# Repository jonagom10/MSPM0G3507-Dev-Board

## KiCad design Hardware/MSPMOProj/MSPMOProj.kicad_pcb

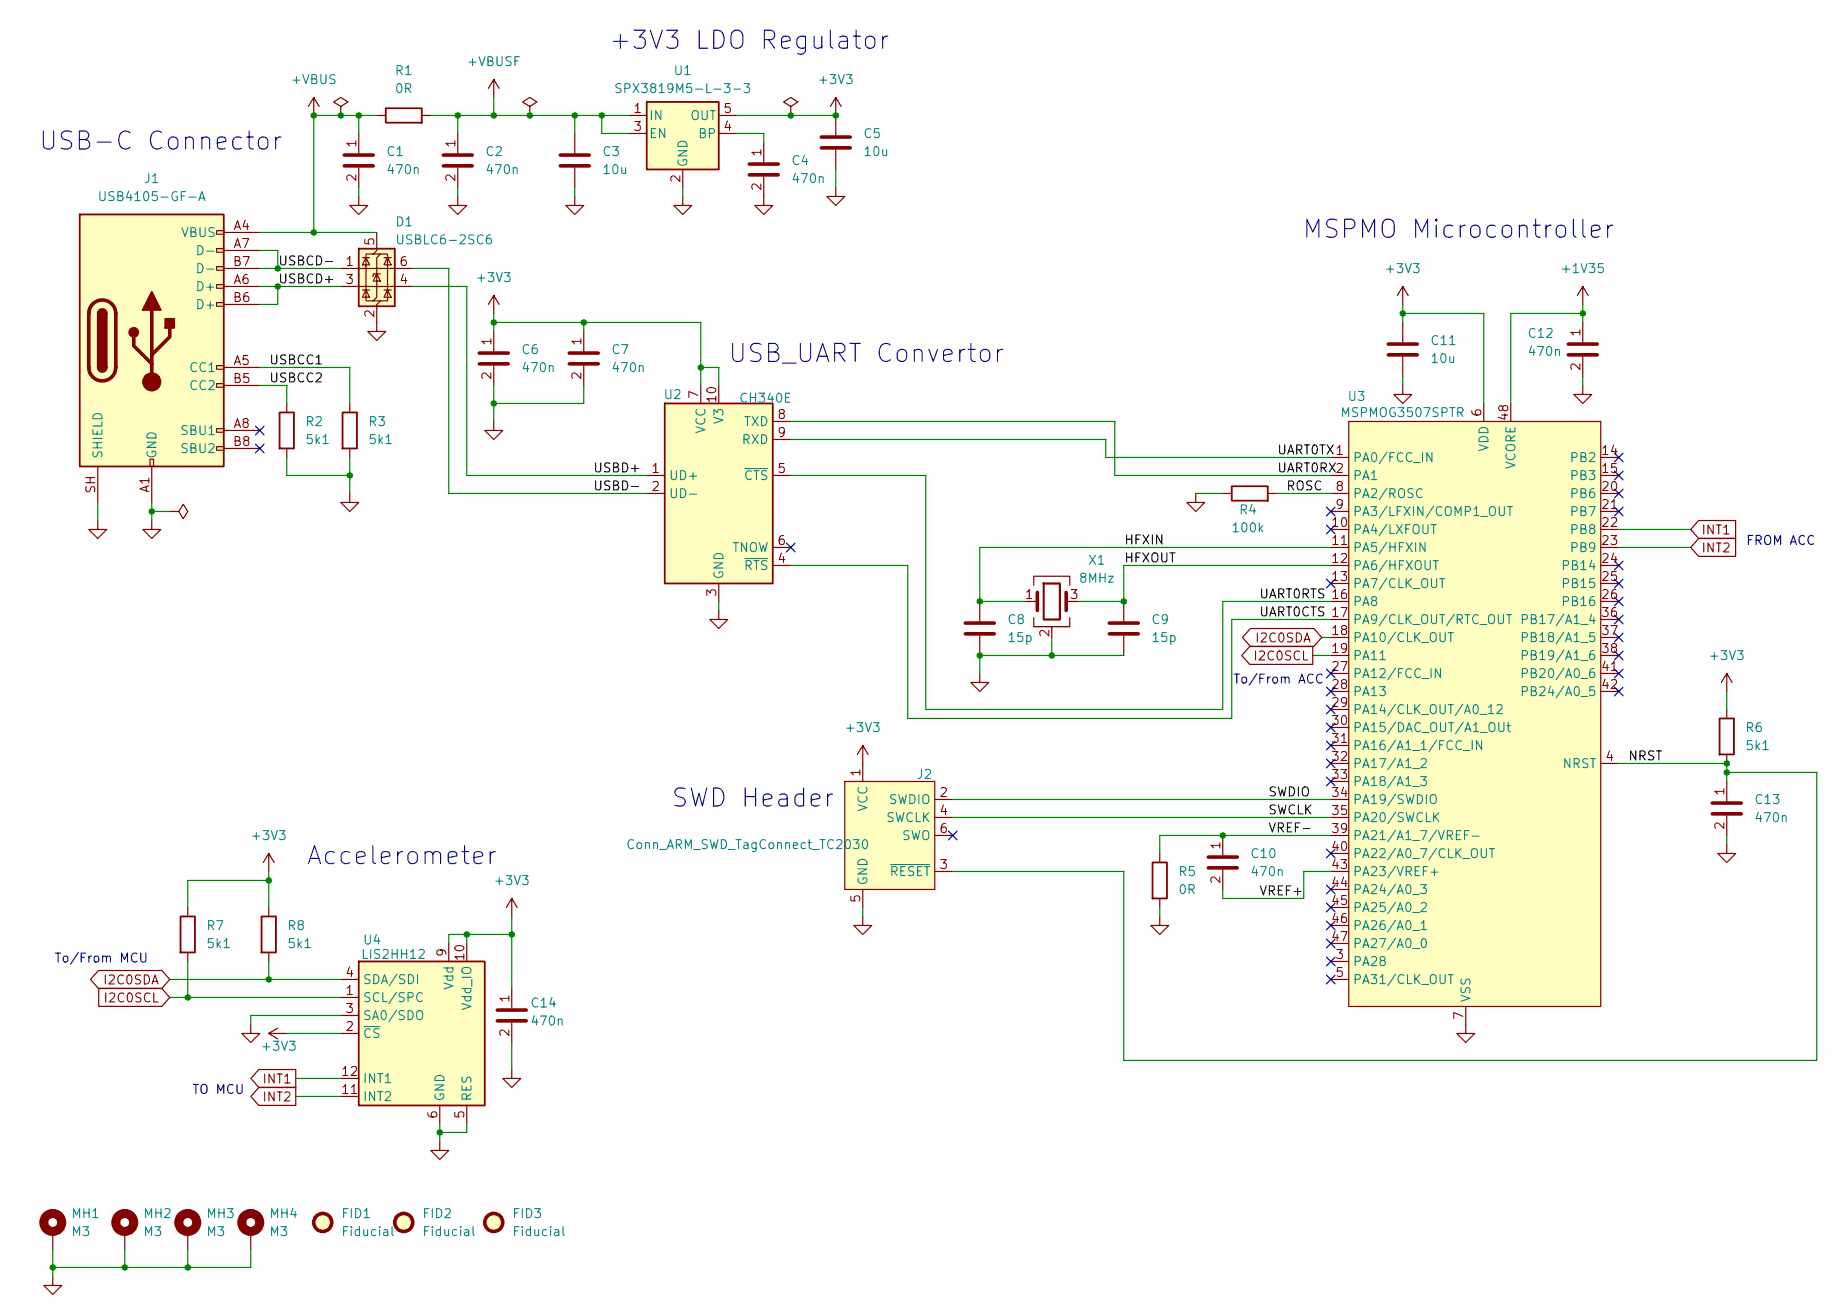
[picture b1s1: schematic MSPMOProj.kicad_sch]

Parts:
C1, C2, C4, C6, C7, C10, C12, C13, C14: 470n; C_0603_1608Metric; Manufacturer Part Number CL10B474KA8NNNC; LCSC Number C1623
C3, C5, C11: 10u; C_0805_2012Metric; Manufacturer Part Number CL21A106KAYNNNE; LCSC C15850
C8, C9: 15p; C_0603_1608Metric; Manufacturer Part Number CL10C150JB8NNNC; LCSC C1644
D1: USBLC6-2SC6; SOT-23-6; Manufacturer Part Number USBLC6-2SC6; LCSC C7519
FID1, FID2, FID3: Fiducial; Fiducial_1mm_Mask2mm
J1: USB4105-GF-A; USB_C_Receptacle_GCT_USB4105-xx-A_16P_TopMnt_Horizontal; Manufacturer Part Number USB4105-GF-A-060; LCSC C3025063
J2: Conn_ARM_SWD_TagConnect_TC2030; Tag-Connect_TC2030-IDC-FP_2x03_P1.27mm_Vertical
MH1, MH2, MH3, MH4: M3; MountingHole_3.2mm_M3_Pad_Via
R1, R5: 0R; R_0603_1608Metric; Manufacturer Part Number 0603WAF0000T5E; LCSC C21189
R2, R3, R6, R7, R8: 5k1; R_0603_1608Metric; Manufacturer Part Number 0603WAF5101T5E; LCSC C23186
R4: 100k; R_0603_1608Metric; Manufacturer Part Number RT0603BRD07100KL; LCSC C122538
U1: SPX3819M5-L-3-3; SOT-23-5; Manufacturer Part Number SPX3819M5-L-3-3/TR; LCSC C9055
U2: CH340E; MSOP-10_3x3mm_P0.5mm; Manufacturer Part Number CH340E; LCSC C99652
U3: MSPMOG3507SPTR; LQFP-48_7x7mm_P0.5mm; Manufacturer Part Number MSPM0G3507SPTR; LCSC C22362630
U4: LIS2HH12; LGA-12_2x2mm_P0.5mm; Manufacturer Part Number LIS2HH12TR; LCSC C221446
X1: 8MHz; Crystal_SMD_3225-4Pin_3.2x2.5mm; Manufacturer Part Number X3S008000FA1H-X; LCSC C254257

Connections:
+1V35: C12.1, U3.48 (VCORE)
+3V3: C5.1, C6.1, C7.1, C11.1, C14.1, J2.1 (VCC), R6.1, R7.1, R8.1, U1.5 (OUT), U2.7 (VCC), U2.10 (V3), U3.6 (VDD), U4.2 (~CS), U4.9 (Vdd), U4.10 (Vdd_IO)
+VBUS: C1.1, D1.5 (VBUS), J1.A4 (VBUS), J1.A9 (VBUS), J1.B4 (VBUS), J1.B9 (VBUS), R1.1
+VBUSF: C2.1, C3.1, R1.2, U1.1 (IN), U1.3 (EN)
/HFXIN: C8.1, U3.11 (PA5/HFXIN), X1.1
/HFXOUT: C9.1, U3.12 (PA6/HFXOUT), X1.3
/NRST: C13.1, J2.3 (~RESET), R6.2, U3.4 (NRST)
/ROSC: R4.2, U3.8 (PA2/ROSC)
/SWCLK: J2.4 (SWCLK), U3.35 (PA20/SWCLK)
/SWDIO: J2.2 (SWDIO), U3.34 (PA19/SWDIO)
/UART0CTS: U2.4 (~RTS), U3.17 (PA9/CLK_OUT/RTC_OUT)
/UART0RTS: U2.5 (~CTS), U3.16 (PA8)
/UART0RX: U2.8 (TXD), U3.2 (PA1)
/UART0TX: U2.9 (RXD), U3.1 (PA0/FCC_IN)
/USBCC1: J1.A5 (CC1), R3.1
/USBCC2: J1.B5 (CC2), R2.1
/USBCD+: D1.3 (I/O2), J1.A6 (D+), J1.B6 (D+)
/USBCD-: D1.1 (I/O1), J1.A7 (D-), J1.B7 (D-)
/USBD+: D1.4 (I/O2), U2.1 (UD+)
/USBD-: D1.6 (I/O1), U2.2 (UD-)
/VREF+: C10.2, U3.43 (PA23/VREF+)
/VREF-: C10.1, R5.1, U3.39 (PA21/A1_7/VREF-)
GND: C1.2, C2.2, C3.2, C4.2, C5.2, C6.2, C7.2, C8.2, C9.2, C11.2, C12.2, C13.2, C14.2, D1.2 (GND), J1.A1 (GND), J1.A12 (GND), J1.B1 (GND), J1.B12 (GND), J1.SH (SHIELD), J2.5 (GND), MH1.1 (1_1), MH2.1 (1_1), MH3.1 (1_1), MH4.1 (1_1), R2.2, R3.2, R4.1, R5.2, U1.2 (GND), U2.3 (GND), U3.7 (VSS), U4.3 (SA0/SDO), U4.5 (RES), U4.6 (GND), U4.7 (GND), U4.8 (GND), X1.2 (G), X1.4 (G)
I2C0SCL: R7.2, U3.19 (PA11), U4.1 (SCL/SPC)
I2C0SDA: R8.2, U3.18 (PA10/CLK_OUT), U4.4 (SDA/SDI)
INT1: U3.22 (PB8), U4.12 (INT1)
INT2: U3.23 (PB9), U4.11 (INT2)
unnamed: C4.1, U1.4 (BP)

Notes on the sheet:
MSPMO Microcontroller
To/From ACC
SWD Header
+3V3 LDO Regulator
USB_UART Convertor
FROM ACC
To/From MCU
USB-C Connector
Accelerometer
TO MCU

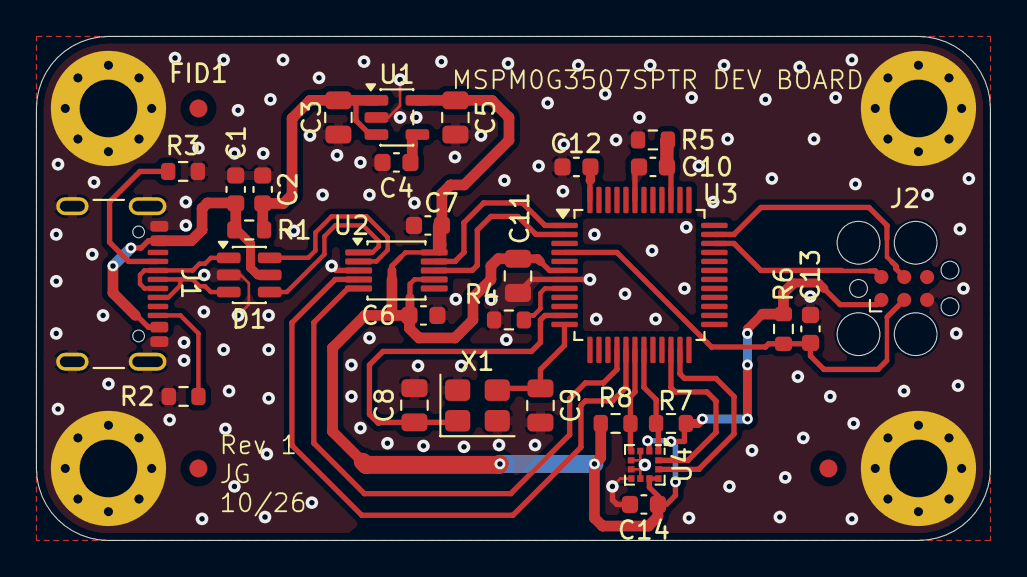
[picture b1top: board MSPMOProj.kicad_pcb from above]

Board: 2 copper layers, 53.0 x 28.0 mm, 37 parts (0 on the bottom side), 28 nets.

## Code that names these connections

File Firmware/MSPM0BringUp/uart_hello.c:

/*
 * Copyright (c) 2021, Texas Instruments Incorporated
 * All rights reserved.
 *
 * Redistribution and use in source and binary forms, with or without
 * modification, are permitted provided that the following conditions
 * are met:
 *
 * *  Redistributions of source code must retain the above copyright
 *    notice, this list of conditions and the following disclaimer.
 *
 * *  Redistributions in binary form must reproduce the above copyright
 *    notice, this list of conditions and the following disclaimer in the
 *    documentation and/or other materials provided with the distribution.
 *
 * *  Neither the name of Texas Instruments Incorporated nor the names of
 *    its contributors may be used to endorse or promote products derived
 *    from this software without specific prior written permission.
 *
 * THIS SOFTWARE IS PROVIDED BY THE COPYRIGHT HOLDERS AND CONTRIBUTORS "AS IS"
 * AND ANY EXPRESS OR IMPLIED WARRANTIES, INCLUDING, BUT NOT LIMITED TO,
 * THE IMPLIED WARRANTIES OF MERCHANTABILITY AND FITNESS FOR A PARTICULAR
 * PURPOSE ARE DISCLAIMED. IN NO EVENT SHALL THE COPYRIGHT OWNER OR
 * CONTRIBUTORS BE LIABLE FOR ANY DIRECT, INDIRECT, INCIDENTAL, SPECIAL,
 * EXEMPLARY, OR CONSEQUENTIAL DAMAGES (INCLUDING, BUT NOT LIMITED TO,
 * PROCUREMENT OF SUBSTITUTE GOODS OR SERVICES; LOSS OF USE, DATA, OR PROFITS;
 * OR BUSINESS INTERRUPTION) HOWEVER CAUSED AND ON ANY THEORY OF LIABILITY,
 * WHETHER IN CONTRACT, STRICT LIABILITY, OR TORT (INCLUDING NEGLIGENCE OR
 * OTHERWISE) ARISING IN ANY WAY OUT OF THE USE OF THIS SOFTWARE,
 * EVEN IF ADVISED OF THE POSSIBILITY OF SUCH DAMAGE.
 */

/*
 * MSPM0G3507 dev board - LIS2HH12 accelerometer readout
 * (I2C sequence adapted from TI's i2c_controller_rw_multibyte_fifo_poll)
 *
 *   UART0: PA0 = TX, PA1 = RX -> CH340 -> USB serial, 115200 8N1
 *   I2C_0: PA10 = SDA, PA11 = SCL -> LIS2HH12 at 0x1E (SA0 = GND)
 *
 * 1. Checks WHO_AM_I (0x0F) == 0x41
 * 2. Enables the sensor: 100 Hz, X/Y/Z on, +/-2 g
 * 3. Prints X/Y/Z in milli-g five times per second
 */

#include "ti_msp_dl_config.h"
#include <stdio.h>
#include <stdint.h>
#include <stdbool.h>

/* ---------------- LIS2HH12 ---------------- */
#define LIS2HH12_ADDR     (0x1E)
#define REG_WHO_AM_I      (0x0F)
#define REG_CTRL1         (0x20)
#define REG_OUT_X_L       (0x28)   /* X_L, X_H, Y_L, Y_H, Z_L, Z_H */
#define WHO_AM_I_VALUE    (0x41)

/* CTRL1 = 0b0011_1111: ODR = 100 Hz, BDU = 1, Z/Y/X enabled */
#define CTRL1_100HZ_XYZ   (0x3F)

/* +/-2 g full scale (default): 0.061 mg per LSB */
#define MG_PER_LSB_X1000  (61)

#define I2C_TIMEOUT       (1000000u)

/* ---------------- globals ---------------- */
static uint32_t gDelayCycles;   /* errata I2C_ERR_13 delay */
static char line[96];

/* ---------------- UART ---------------- */
static void uart_puts(const char *s)
{
    while (*s) {
        DL_UART_Main_transmitDataBlocking(UART_0_INST, *s++);
    }
}

static void fail(const char *msg)
{
    uart_puts(msg);
    snprintf(line, sizeof line, "  (I2C status = 0x%08lX)\r\n",
             (unsigned long) DL_I2C_getControllerStatus(I2C_0_INST));
    uart_puts(line);
    while (1) {
    }
}

/* ---------------- I2C helpers ---------------- */

/* Same delay calculation as TI's example (errata I2C_ERR_13) */
static void i2c_setup_delay(void)
{
    DL_I2C_ClockConfig cfg;
    uint32_t clkFreq = 32000000;

    DL_I2C_getClockConfig(I2C_0_INST, &cfg);
    if (cfg.clockSel == DL_I2C_CLOCK_MFCLK) {
        clkFreq = 4000000;
    }
    gDelayCycles = (3 * (cfg.divideRatio + 1)) * (CPUCLK_FREQ / clkFreq);
}

static bool i2c_wait_idle(void)
{
    uint32_t t = I2C_TIMEOUT;
    while (!(DL_I2C_getControllerStatus(I2C_0_INST) &
             DL_I2C_CONTROLLER_STATUS_IDLE)) {
        if (--t == 0) return false;
    }
    return true;
}

static bool i2c_wait_not_busy(void)
{
    uint32_t t = I2C_TIMEOUT;
    while (DL_I2C_getControllerStatus(I2C_0_INST) &
           DL_I2C_CONTROLLER_STATUS_BUSY) {
        if (--t == 0) return false;
    }
    return true;
}

/* Write len bytes (max 8, the FIFO size). buf[0] is the register address. */
static bool i2c_write(const uint8_t *buf, uint8_t len)
{
    if (!i2c_wait_idle()) return false;

    DL_I2C_flushControllerTXFIFO(I2C_0_INST);
    DL_I2C_fillControllerTXFIFO(I2C_0_INST, (uint8_t *) buf, len);
    DL_I2C_startControllerTransfer(I2C_0_INST, LIS2HH12_ADDR,
        DL_I2C_CONTROLLER_DIRECTION_TX, len);
    delay_cycles(gDelayCycles);

    if (!i2c_wait_not_busy()) return false;
    if (DL_I2C_getControllerStatus(I2C_0_INST) &
        DL_I2C_CONTROLLER_STATUS_ERROR) {
        return false;   /* NACK */
    }
    return i2c_wait_idle();
}

/* Read len bytes (max 8) into data. */
static bool i2c_read(uint8_t *data, uint8_t len)
{
    if (!i2c_wait_idle()) return false;

    DL_I2C_startControllerTransfer(I2C_0_INST, LIS2HH12_ADDR,
        DL_I2C_CONTROLLER_DIRECTION_RX, len);
    delay_cycles(gDelayCycles);

    for (uint8_t i = 0; i < len; i++) {
        uint32_t t = I2C_TIMEOUT;
        while (DL_I2C_isControllerRXFIFOEmpty(I2C_0_INST)) {
            if (--t == 0) return false;
        }
        data[i] = DL_I2C_receiveControllerData(I2C_0_INST);
    }

    if (!i2c_wait_not_busy()) return false;
    return i2c_wait_idle();
}

/* ---------------- LIS2HH12 helpers ---------------- */
static bool lis_write_reg(uint8_t reg, uint8_t value)
{
    uint8_t buf[2] = { reg, value };
    return i2c_write(buf, 2);
}

/* Read consecutive registers. The LIS2HH12 auto-increments the register
 * address by default (CTRL4.IF_ADD_INC = 1). */
static bool lis_read_regs(uint8_t reg, uint8_t *data, uint8_t len)
{
    if (!i2c_write(&reg, 1)) return false;   /* set register pointer */
    delay_cycles(1000);
    return i2c_read(data, len);
}

/* ---------------- main ---------------- */
int main(void)
{
    SYSCFG_DL_init();
    i2c_setup_delay();
    uart_puts("\r\nMSPM0 board: LIS2HH12 accelerometer\r\n");

    /* 1. Identify the sensor */
    uint8_t who = 0;
    if (!lis_read_regs(REG_WHO_AM_I, &who, 1)) {
        fail("I2C error reading WHO_AM_I\r\n");
    }
    snprintf(line, sizeof line, "WHO_AM_I = 0x%02X\r\n", who);
    uart_puts(line);
    if (who != WHO_AM_I_VALUE) {
        fail("Unexpected WHO_AM_I value\r\n");
    }

    /* 2. Power it on: 100 Hz, X/Y/Z enabled */
    if (!lis_write_reg(REG_CTRL1, CTRL1_100HZ_XYZ)) {
        fail("I2C error writing CTRL1\r\n");
    }

    /* Read CTRL1 back to confirm the write took */
    uint8_t ctrl1 = 0;
    if (lis_read_regs(REG_CTRL1, &ctrl1, 1)) {
        snprintf(line, sizeof line, "CTRL1 = 0x%02X (expect 0x3F)\r\n", ctrl1);
        uart_puts(line);
    }

    delay_cycles(CPUCLK_FREQ / 50);   /* ~20 ms for the first samples */

    /* 3. Stream X/Y/Z in milli-g */
    while (1) {
        uint8_t raw[6];

        if (lis_read_regs(REG_OUT_X_L, raw, 6)) {
            int16_t x = (int16_t) ((raw[1] << 8) | raw[0]);
            int16_t y = (int16_t) ((raw[3] << 8) | raw[2]);
            int16_t z = (int16_t) ((raw[5] << 8) | raw[4]);

            long x_mg = (long) x * MG_PER_LSB_X1000 / 1000;
            long y_mg = (long) y * MG_PER_LSB_X1000 / 1000;
            long z_mg = (long) z * MG_PER_LSB_X1000 / 1000;

            snprintf(line, sizeof line, "X = %6ld   Y = %6ld   Z = %6ld  mg\r\n",
                     x_mg, y_mg, z_mg);
            uart_puts(line);
        } else {
            uart_puts("I2C read error\r\n");
        }

        delay_cycles(CPUCLK_FREQ / 5);   /* ~200 ms */
    }
}
